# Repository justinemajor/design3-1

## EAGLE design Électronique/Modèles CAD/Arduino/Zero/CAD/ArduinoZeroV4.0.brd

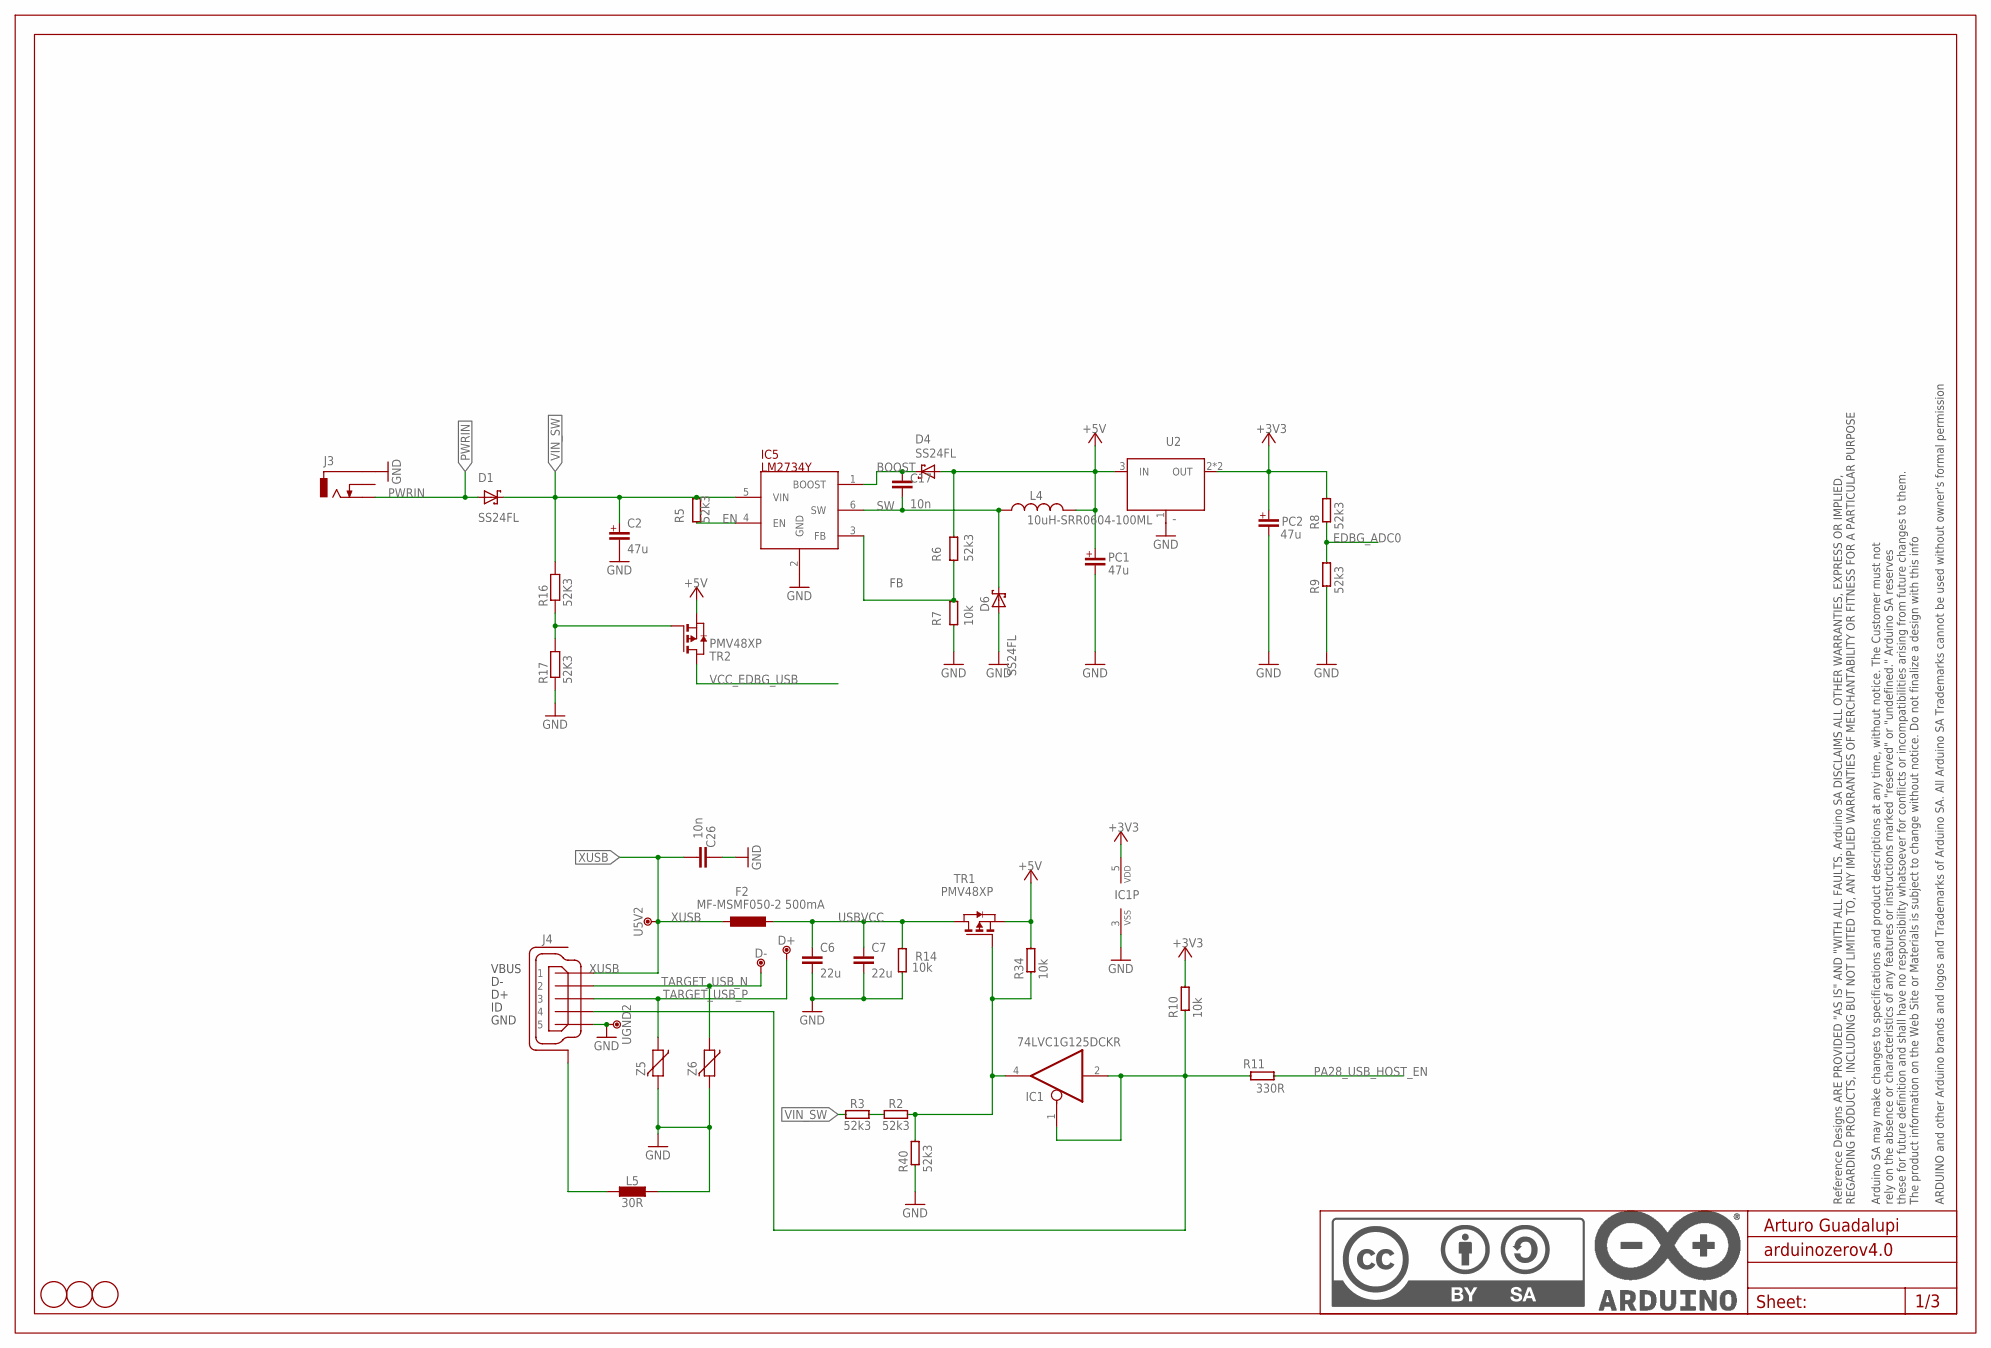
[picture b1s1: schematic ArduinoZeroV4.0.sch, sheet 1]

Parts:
C2: 47u; PANASONIC_D
C6, C7: 22u; 0805-R2013X50N
C17: 10n; 0603-1608X90N
C26: 10n; C0603-ROUND
D1, D4, D6: SS24FL; SOD123F
D+: DNP; TP-1.00MM
D-: DNP; TP-1.00MM
F2: MF-MSMF050-2 500mA; L1812
FD1, FD2, FD3: DNP; FD-1-1.5
IC1: 74LVC1G125DCKR; SC70-5
IC5: LM2734Y; SOT23-6
J3: -; POWERSUPPLY_DC-21MM
J4: -; ZX62-AB-5PA
L4: 10uH-SRR0604-100ML; SRR0604
L5: 30R; 0805-R2013X50N
PC1, PC2: 47u; PANASONIC_D
R2, R3, R5, R6, R8, R9, R40: 52k3; C0603
R7, R10, R14, R34: 10k; C0603
R11: 330R; C0603
R16, R17: 52K3; R0603-ROUND
TR1, TR2: PMV48XP; SOT-23
U2: -; SOT223
U5V2: DNP; TP-1.00MM
U$4: DNP; FRAME
UGND2: DNP; TP-1.00MM
Z5, Z6: -; C0603

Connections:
+3V3: IC1.5 (VDD), PC2.+, R8.2, R10.2, U2.2 (OUT), U2.4 (OUT); also elsewhere on the board
+5V: D4.A, L4.P$2 (2), PC1.+, R6.1, R34.2, TR1.2 (S), TR2.2 (S), U2.3 (IN); also elsewhere on the board
BOOST: C17.1, D4.C, IC5.1 (BOOST)
EDBG_ADC0: R8.1, R9.2; also elsewhere on the board
EN: IC5.4 (EN), R5.2
FB: IC5.3 (FB), R6.2, R7.1
GND: C2.-, C6.2, C7.2, C26.2, D6.A, IC1.3 (VSS), IC5.2 (GND), J3.-1 (1), J3.-2 (1), J3.-3 (1), J4.5, L5.2, PC1.-, PC2.-, R7.2, R9.1, R14.1, R17.1, R40.1, U2.1 (GND/ADJ), UGND2.X, Z5.2, Z6.2; also elsewhere on the board
unnamed: IC1.4 (O), R2.2, R34.1, R40.2, TR1.3 (G)
unnamed: R2.1, R3.2
unnamed: IC1.1 (OE), IC1.2 (I), J4.4, R10.1, R11.1
unnamed: J4.6 (SH), J4.7 (SH), J4.8 (SH), J4.9 (SH), J4.10 (SH), J4.11 (SH), L5.1
unnamed: R16.1, R17.2, TR2.3 (G)
PA28_USB_HOST_EN: R11.2; also elsewhere on the board
PWRIN: D1.A, J3.+1 (3), J3.+2 (3), J3.+3 (3); also elsewhere on the board
SW: C17.2, D6.C, IC5.6 (SW), L4.P$1 (1)
TARGET_USB_N: D-.X, J4.2, Z6.1; also elsewhere on the board
TARGET_USB_P: D+.X, J4.3, Z5.1; also elsewhere on the board
USBVCC: C6.1, C7.1, F2.1, R14.2, TR1.1 (D)
VCC_EDBG_USB: TR2.1 (D); also elsewhere on the board
VIN_SW: C2.+, D1.C, IC5.5 (VIN), R3.1, R5.1, R16.2
XUSB: C26.1, F2.2, J4.1, U5V2.X

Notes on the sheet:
Arturo Guadalupi

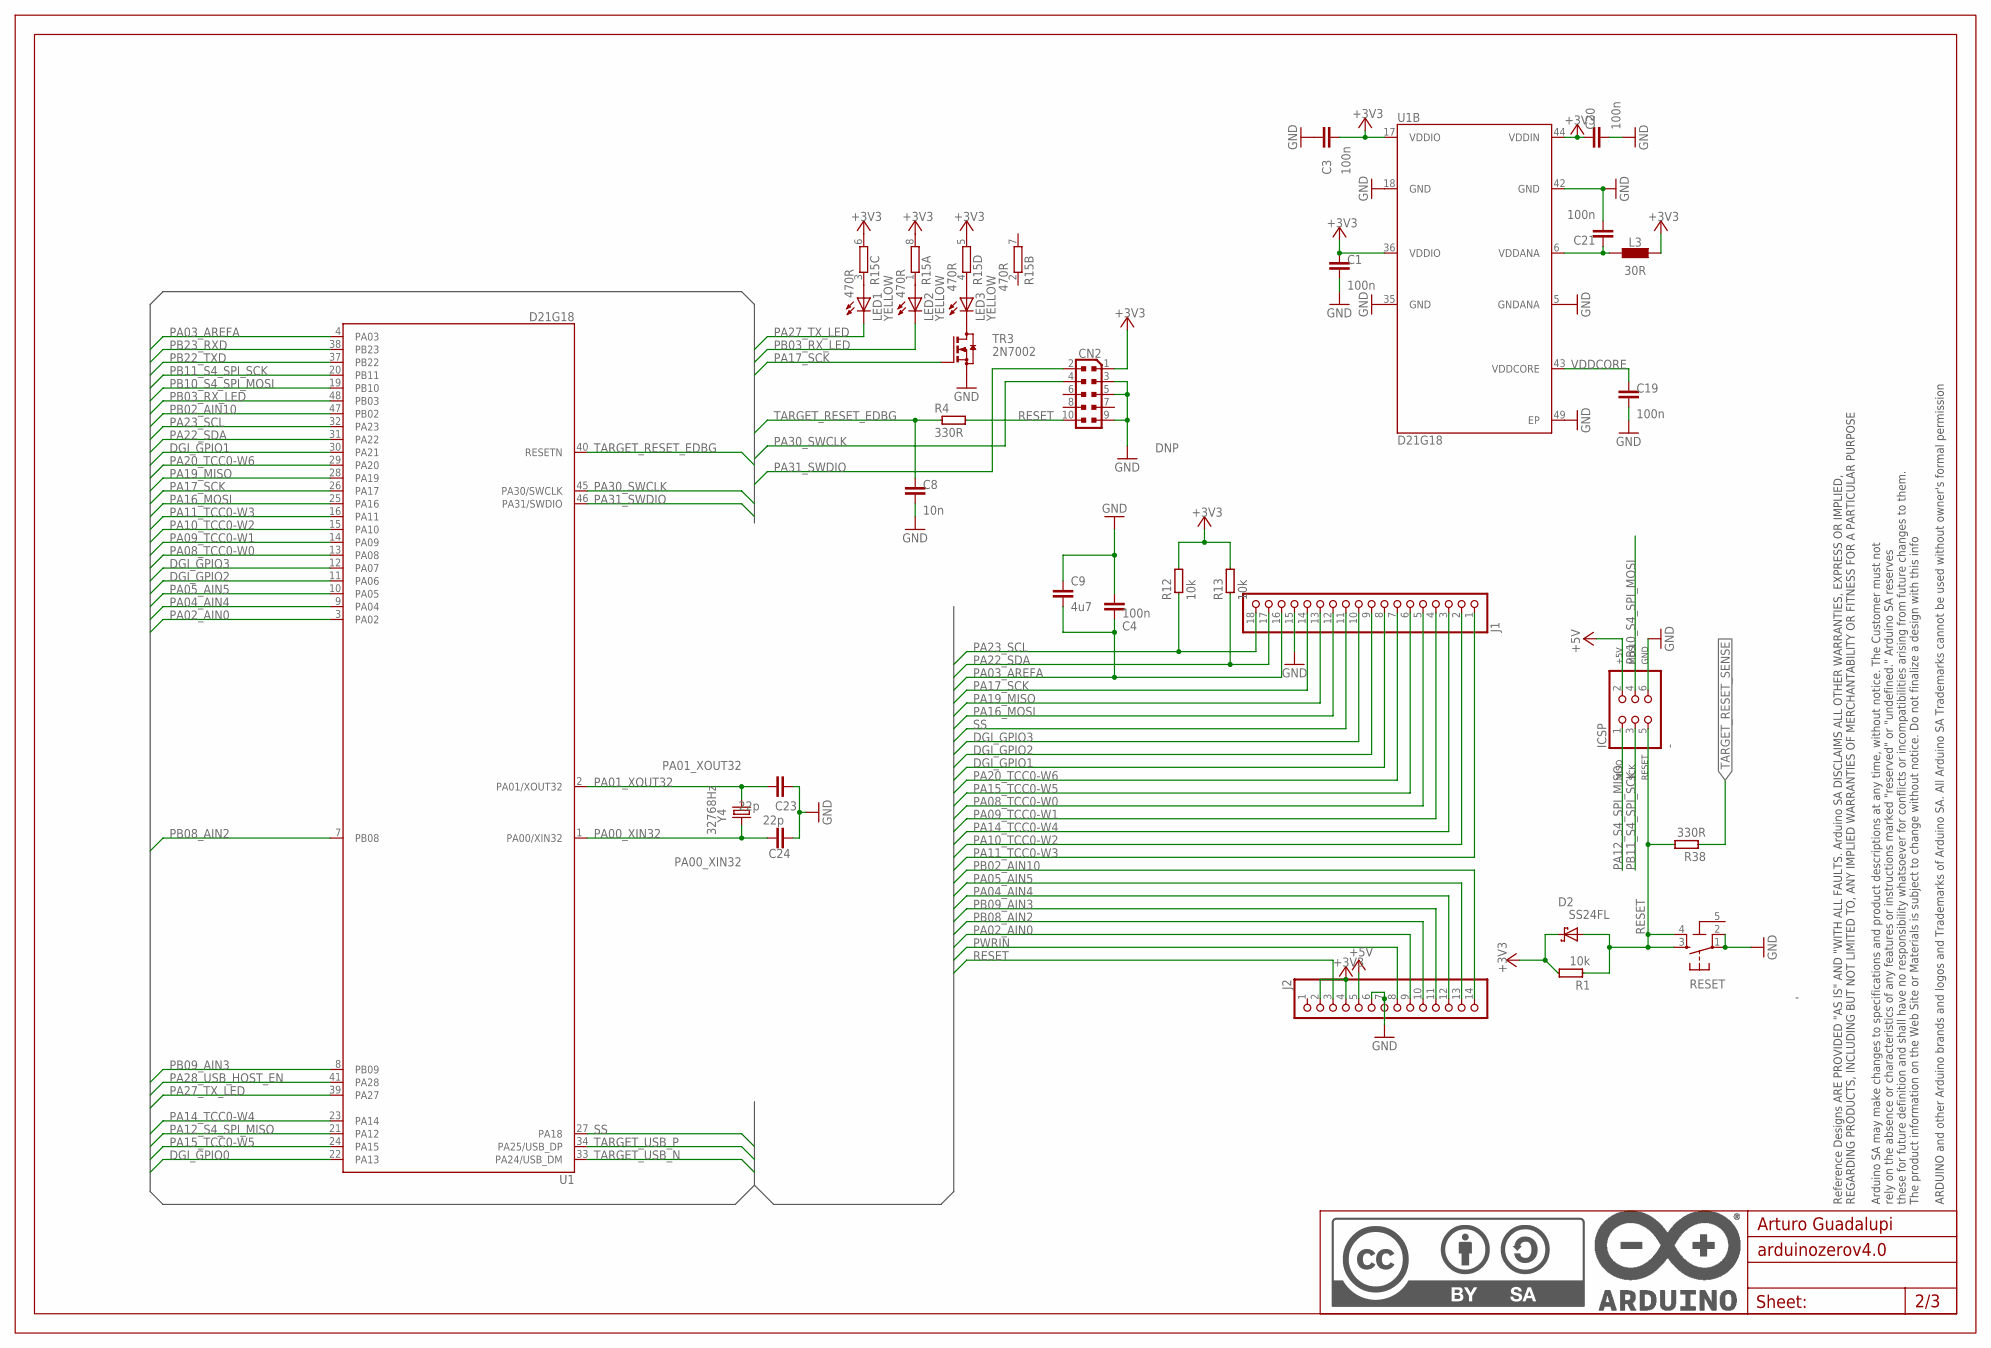
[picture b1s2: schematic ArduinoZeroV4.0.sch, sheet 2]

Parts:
C1, C3, C19, C20, C21: 100n; 0603-1608X90N
C4: 100n; 0402-1005X55N
C8: 10n; 0603-1608X90N
C9: 4u7; 0603-1608X90N
C23, C24: 22p; 0603-1608X90N
CN2: DNP; PINHEAD_2X05_127
D2: SS24FL; SOD123F
ICSP: -; 2X03
J1: -; 1X18-CUSTOM
J2: -; 1X14-CUSTOM
L3: 30R; 0805-R2013X50N
LED1, LED2, LED3: YELLOW; CHIPLED_0805
R1, R12, R13: 10k; C0603
R4, R38: 330R; C0603
R15: 470R; CAY16
RESET: -; TS42
TR3: 2N7002; SOT23
U1: D21G18; QFN50P700X700X90-49XN-EPSQ515
U$5: DNP; FRAME
Y4: 32768Hz; ABS07

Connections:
5-GND: RESET.5 (5-GND)
+3V3: C1.1, C3.2, C20.1, CN2.1, D2.C, J2.2, J2.4, L3.2, R1.2, R12.2, R13.2, R15.5 (2), R15.6 (2), R15.8 (2), U1.17 (VDDIO), U1.36 (VDDIO), U1.44 (VDDIN); also elsewhere on the board
+5V: ICSP.2, J2.5; also elsewhere on the board
DGI_GPIO0: U1.22 (PA13); also elsewhere on the board
DGI_GPIO1: J1.8, U1.30 (PA21); also elsewhere on the board
DGI_GPIO2: J1.9, U1.11 (PA06); also elsewhere on the board
DGI_GPIO3: J1.10, U1.12 (PA07); also elsewhere on the board
GND: C1.2, C3.1, C4.2, C8.2, C9.1, C19.2, C20.2, C21.2, C23.1, C24.1, CN2.3, CN2.5, CN2.9, ICSP.6, J1.15, J2.6, J2.7, RESET.1, RESET.2, TR3.2 (S), U1.5 (GNDANA), U1.18 (GND), U1.35 (GND), U1.42 (GND), U1.49 (EP); also elsewhere on the board
unnamed: LED3.C, TR3.3 (D)
unnamed: C21.1, L3.1, U1.6 (VDDANA)
unnamed: LED1.A, R15.3 (1)
unnamed: LED2.A, R15.1
unnamed: LED3.A, R15.4 (1)
PA00_XIN32: C24.2, U1.1 (PA00/XIN32), Y4.1
PA01_XOUT32: C23.2, U1.2 (PA01/XOUT32), Y4.2
PA02_AIN0: J2.9, U1.3 (PA02)
PA03_AREFA: C4.1, C9.2, J1.16, U1.4 (PA03)
PA04_AIN4: J2.12, U1.9 (PA04)
PA05_AIN5: J2.13, U1.10 (PA05)
PA08_TCC0-W0: J1.5, U1.13 (PA08)
PA09_TCC0-W1: J1.4, U1.14 (PA09)
PA10_TCC0-W2: J1.2, U1.15 (PA10)
PA11_TCC0-W3: J1.1, U1.16 (PA11)
PA12_S4_SPI_MISO: ICSP.1, U1.21 (PA12)
PA14_TCC0-W4: J1.3, U1.23 (PA14)
PA15_TCC0-W5: J1.6, U1.24 (PA15)
PA16_MOSI: J1.12, U1.25 (PA16); also elsewhere on the board
PA17_SCK: J1.14, TR3.1 (G), U1.26 (PA17); also elsewhere on the board
PA19_MISO: J1.13, U1.28 (PA19); also elsewhere on the board
PA20_TCC0-W6: J1.7, U1.29 (PA20)
PA22_SDA: J1.17, R13.1, U1.31 (PA22); also elsewhere on the board
PA23_SCL: J1.18, R12.1, U1.32 (PA23); also elsewhere on the board
PA27_TX_LED: LED1.C, U1.39 (PA27)
PA28_USB_HOST_EN: U1.41 (PA28); also elsewhere on the board
PA30_SWCLK: CN2.4, U1.45 (PA30/SWCLK); also elsewhere on the board
PA31_SWDIO: CN2.2, U1.46 (PA31/SWDIO); also elsewhere on the board
PB02_AIN10: J2.14, U1.47 (PB02)
PB03_RX_LED: LED2.C, U1.48 (PB03)
PB08_AIN2: J2.10, U1.7 (PB08)
PB09_AIN3: J2.11, U1.8 (PB09)
PB10_S4_SPI_MOSI: ICSP.4, U1.19 (PB10)
PB11_S4_SPI_SCK: ICSP.3, U1.20 (PB11)
PB22_TXD: U1.37 (PB22); also elsewhere on the board
PB23_RXD: U1.38 (PB23); also elsewhere on the board
PWRIN: J2.8; also elsewhere on the board
RESET: CN2.10, D2.A, ICSP.5, J2.3, R1.1, R4.2, R38.2, RESET.3, RESET.4
SS: J1.11, U1.27 (PA18); also elsewhere on the board
TARGET_RESET_EDBG: C8.1, R4.1, U1.40 (RESETN); also elsewhere on the board
TARGET_RESET_SENSE: R38.1; also elsewhere on the board
TARGET_USB_N: U1.33 (PA24/USB_DM); also elsewhere on the board
TARGET_USB_P: U1.34 (PA25/USB_DP); also elsewhere on the board
VDDCORE: C19.1, U1.43 (VDDCORE)

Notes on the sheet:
Arturo Guadalupi

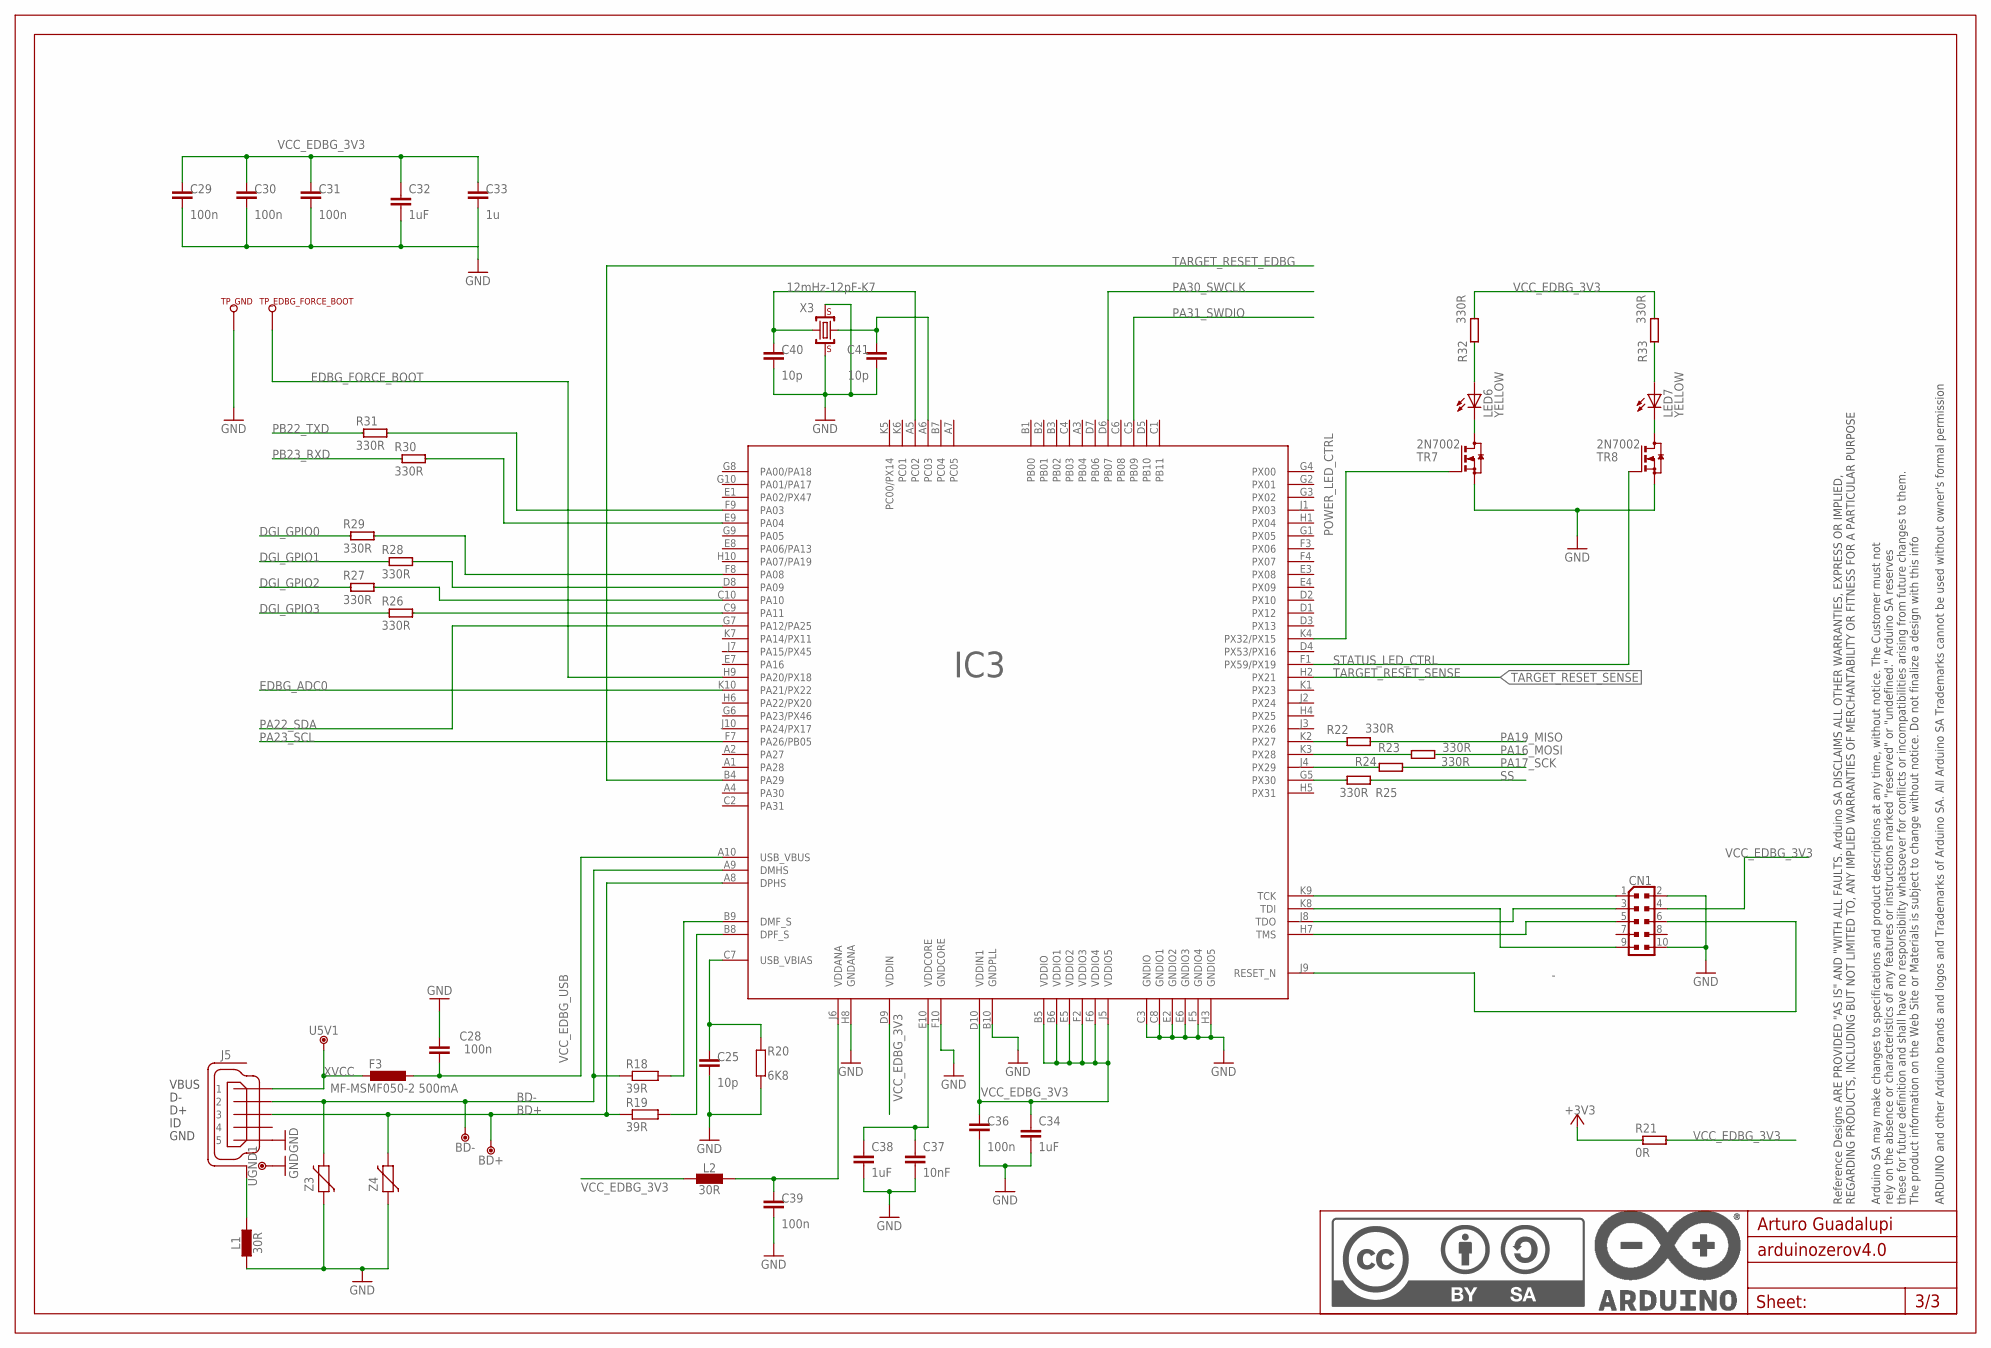
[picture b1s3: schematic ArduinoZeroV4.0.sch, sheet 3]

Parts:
BD+: DNP; TP-1.00MM
BD-: DNP; TP-1.00MM
C25, C40, C41: 10p; 0603-1608X90N
C28, C29, C30, C31, C36, C39: 100n; 0603-1608X90N
C32, C34, C38: 1uF; C0603-ROUND
C33: 1u; 0603-1608X90N
C37: 10nF; C0603-ROUND
CN1: -; PINHEAD_2X05_127
F3: MF-MSMF050-2 500mA; L1812
IC3: 1791_AT32UC3A4256HHB-C1UR; VFBGA100
J5: -; ZX62-AB-5PA
L1, L2: 30R; 0805-R2013X50N
LED6, LED7: YELLOW; CHIPLED_0805
R18, R19: 39R; R0603-ROUND
R20: 6K8; R0603-ROUND
R21: 0R; C0603
R22, R23, R24, R25, R26, R27, R28, R29, R30, R31, R32, R33: 330R; C0603
TP_EDBG_FORCE_BOOT: TP_SP; TP-SP
TP_GND: TP_SP; TP-SP
TR7, TR8: 2N7002; SOT23
U5V1: DNP; TP-1.00MM
U$6: DNP; FRAME
UGND1: DNP; TP-1.00MM
X3: 12mHz-12pF-K7; CRYSTAL-3.2-2.5
Z3, Z4: -; C0603

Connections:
+3V3: R21.1; also elsewhere on the board
BD+: BD+.X, IC3.A8 (DPHS), J5.3, R19.1, Z4.2
BD-: BD-.X, IC3.A9 (DMHS), J5.2, R18.1, Z3.2
DGI_GPIO0: R29.1; also elsewhere on the board
DGI_GPIO1: R28.1; also elsewhere on the board
DGI_GPIO2: R27.1; also elsewhere on the board
DGI_GPIO3: R26.1; also elsewhere on the board
EDBG_ADC0: IC3.K10 (PA21/PX22); also elsewhere on the board
EDBG_FORCE_BOOT: IC3.H9 (PA20/PX18), TP_EDBG_FORCE_BOOT.X
GND: C25.2, C28.2, C29.2, C30.2, C31.2, C32.2, C33.2, C34.2, C36.2, C37.2, C38.2, C39.2, C40.2, C41.2, CN1.2, CN1.10, IC3.B10 (GNDPLL), IC3.C3 (GNDIO), IC3.C8 (GNDIO1), IC3.E2 (GNDIO2), IC3.E6 (GNDIO3), IC3.F5 (GNDIO4), IC3.F10 (GNDCORE), IC3.H3 (GNDIO5), IC3.H8 (GNDANA), J5.5, L1.1, R20.1, TP_GND.X, TR7.2 (S), TR8.2 (S), UGND1.X, X3.2 (GND), X3.4 (GND), Z3.1, Z4.1; also elsewhere on the board
unnamed: LED6.C, TR7.3 (D)
unnamed: LED7.C, TR8.3 (D)
unnamed: J5.6 (SH), J5.7 (SH), J5.8 (SH), J5.9 (SH), J5.10 (SH), J5.11 (SH), L1.2
unnamed: IC3.B9 (DMF_S), R18.2
unnamed: IC3.B8 (DPF_S), R19.2
unnamed: C25.1, IC3.C7 (USB_VBIAS), R20.2
unnamed: C41.1, IC3.A6 (PC03), X3.1 (C1)
unnamed: C40.1, IC3.A5 (PC02), X3.3 (C2)
unnamed: C37.1, C38.1, IC3.E10 (VDDCORE)
unnamed: C39.1, IC3.J6 (VDDANA), L2.2
unnamed: IC3.K2 (PX27), R22.1
unnamed: IC3.K3 (PX28), R23.1
unnamed: IC3.J4 (PX29), R24.1
unnamed: IC3.G5 (PX30), R25.1
unnamed: IC3.C9 (PA11), R26.2
unnamed: IC3.C10 (PA10), R27.2
unnamed: IC3.D8 (PA09), R28.2
unnamed: IC3.F8 (PA08), R29.2
unnamed: IC3.E9 (PA04), R30.2
unnamed: IC3.F9 (PA03), R31.2
unnamed: CN1.1, IC3.K9 (TCK)
unnamed: CN1.9, IC3.K8 (TDI)
unnamed: CN1.3, IC3.J8 (TDO)
unnamed: CN1.5, IC3.H7 (TMS)
unnamed: CN1.6, IC3.J9 (RESET_N)
unnamed: LED6.A, R32.1
unnamed: LED7.A, R33.1
PA16_MOSI: R23.2; also elsewhere on the board
PA17_SCK: R24.2; also elsewhere on the board
PA19_MISO: R22.2; also elsewhere on the board
PA22_SDA: IC3.G7 (PA12/PA25); also elsewhere on the board
PA23_SCL: IC3.F7 (PA26/PB05); also elsewhere on the board
PA30_SWCLK: IC3.D6 (PB07); also elsewhere on the board
PA31_SWDIO: IC3.C5 (PB09); also elsewhere on the board
PB22_TXD: R31.1; also elsewhere on the board
PB23_RXD: R30.1; also elsewhere on the board
POWER_LED_CTRL: IC3.K4 (PX32/PX15), TR7.1 (G)
SS: R25.2; also elsewhere on the board
STATUS_LED_CTRL: IC3.F1 (PX59/PX19), TR8.1 (G)
TARGET_RESET_EDBG: IC3.B4 (PA29); also elsewhere on the board
TARGET_RESET_SENSE: IC3.H2 (PX21); also elsewhere on the board
VCC_EDBG_3V3: C29.1, C30.1, C31.1, C32.1, C33.1, C34.1, C36.1, CN1.4, IC3.B5 (VDDIO), IC3.B6 (VDDIO1), IC3.D9 (VDDIN), IC3.D10 (VDDIN1), IC3.E5 (VDDIO2), IC3.F2 (VDDIO3), IC3.F6 (VDDIO4), IC3.J5 (VDDIO5), L2.1, R21.2, R32.2, R33.2
VCC_EDBG_USB: C28.1, F3.1, IC3.A10 (USB_VBUS); also elsewhere on the board
XVCC: F3.2, J5.1, U5V1.X

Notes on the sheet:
Arturo Guadalupi

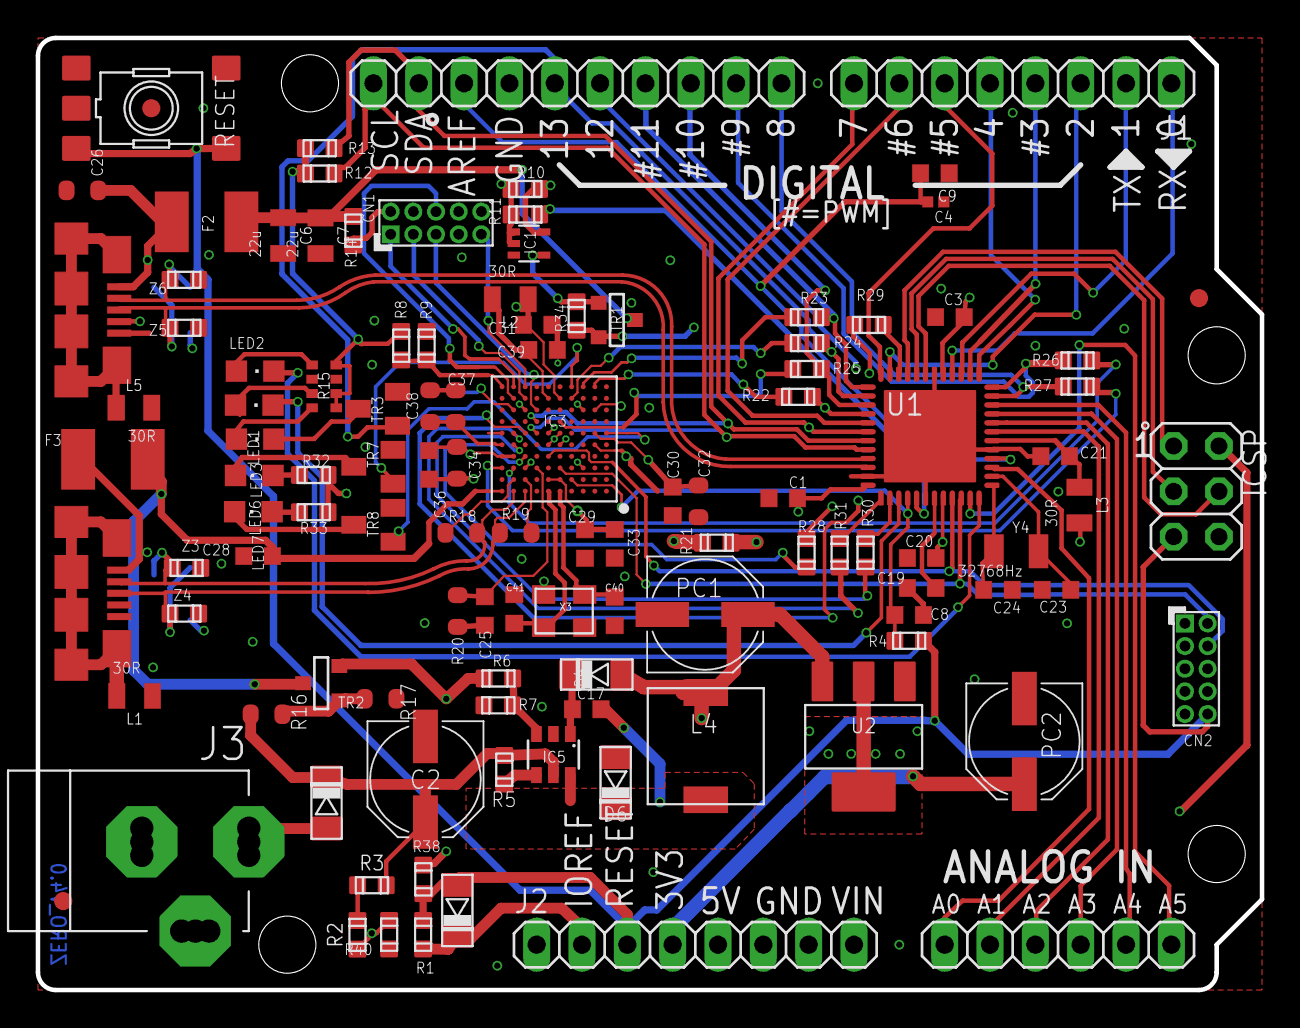
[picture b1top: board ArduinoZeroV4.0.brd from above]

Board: 4 copper layers, 68.6 x 53.3 mm, 124 parts (0 on the bottom side), 99 nets.

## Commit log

2023-02-03 Add electronics and programing workspace
2023-02-03 Add .gitignore
2023-02-03 fixed untracked files
2023-02-03 .gitignore is now working
2023-02-03 Add Arduino C codes and functions
2023-02-04 Create Conception mécanique
2023-02-04 Create Design solidworks
2023-02-06 Add C header files and volt - temp conv code
2023-02-07 Added signal processing formulas
2023-02-07 Add docstring to jupyter notebook
2023-02-07 Jupyter - try experimental values
2023-02-09 Added current calculation and new PCB
2023-02-09 Added thermistor datasheet
2023-02-10 Completed thermistors array
2023-02-11 Modified Weatstone Vg equation
2023-02-12 Vout(T) simmulation
2023-02-12 Add A/D performance plot
2023-02-13 Updated schematics and PCB
2023-02-15 Altium and Jupyter content update
2023-02-20 Completed thermistors PCB
2023-02-21 Create Design #2
2023-02-21 Create Yo
2023-02-23 Semi-final main PCB schematics
2023-02-27 Routed PCB and added budget excel sheet
2023-02-27 Electronic folders cleanup
2023-03-02 Updated budget and PCB
2023-03-03 Add files via upload
    Le fichier Laser10mm est un cylindre qui agit comme le laser et qui a en fait de 5 mm de diamètre placé devant la lentille.
2023-03-04 Create bruh
2023-03-05 PCB Checkpoint
2023-03-05 Git cleanup
2023-03-05 Git cleanup (again)
2023-03-08 Added electronic CAD models
2023-03-08 Added MCU schematics
2023-03-10 Added CAD files
2023-03-12 Added mounting points
2023-03-12 Forgot gitignore
2023-03-13 Thermistors PCB completed
2023-03-13 Moved Standoffs
2023-03-17 4 Layers PCB Done
2023-03-21 Final Board
2023-03-23 Create Design final
2023-03-30 Updated thermistor modelisation
2023-03-30 Change dir name
2023-03-31 Fixed invalid directory
2023-03-31 Updated Arduino Codes

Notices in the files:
Électronique/Modèles CAD/Arduino/Zero/CAD/ArduinoZeroV4.0.brd:
Copyright (c) 2016-2017 Arduino LLC.  All right reserved. EAGLE Design Rules
parts and their libraries:
Arduino-utility: Copyright (c) 2016-2017 Arduino LLC.  All right reserved.
